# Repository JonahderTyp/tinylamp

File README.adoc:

= tinylamp
Jonah Wille

The tinylamp is a small Headlamp using an ATtiny processor. It is Specifically designed for Scouts, it Features:

* Li-Ion rechargeable Battery
* Charging via Mini-Usb <<Why Mini-Usb?>>

A headlamp specifically designed for scouts

== Overview

image::doc/UserManual/pages/figures/case.png[alt]

== Design Decisions:

=== Why Mini-Usb?

Mini USB is a very durable connector, while USB-C is very susceptible to dust and dirt. Furthermore, Mini USB is easy to handsolder using hot air.

[CAUTION]
The charging port does not comply to USB standards, check schematic for further information.

== TO DOs
* [ ] Headband
* [ ] Inter Lamp Communication

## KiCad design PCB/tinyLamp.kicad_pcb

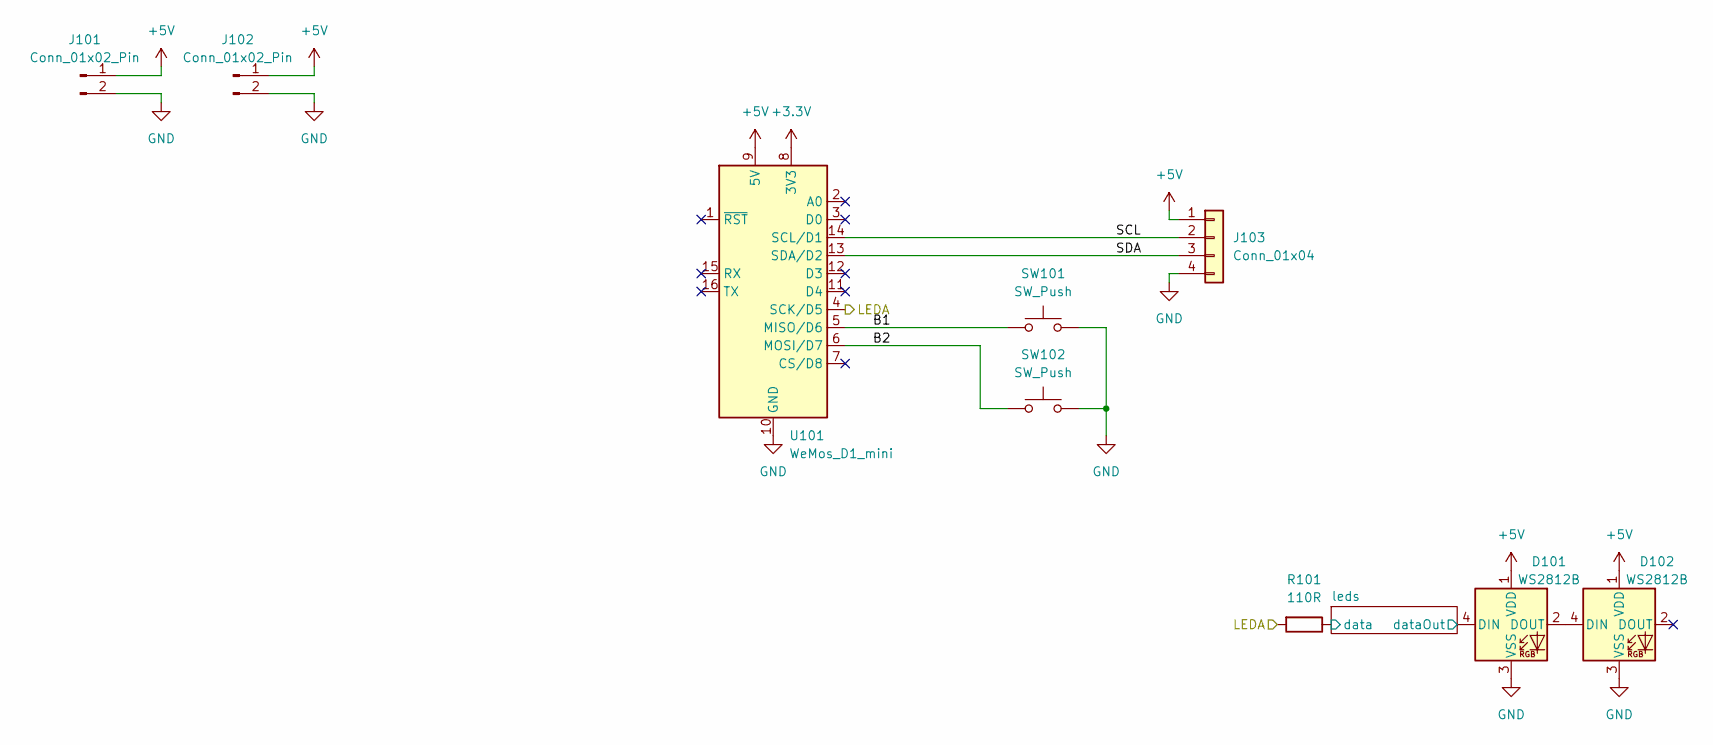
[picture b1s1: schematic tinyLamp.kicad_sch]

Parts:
D101, D102: WS2812B; LED_WS2812B_PLCC4_5.0x5.0mm_P3.2mm
J101, J102: Conn_01x02_Pin; PinHeader_1x02_P2.54mm_Vertical
J103: Conn_01x04; PinHeader_1x04_P2.54mm_Vertical
R101: 110R; R_Axial_DIN0207_L6.3mm_D2.5mm_P10.16mm_Horizontal
SW101, SW102: SW_Push; SW_SPST_PTS647_Sx50
U101: WeMos_D1_mini; WEMOS_D1_mini_light

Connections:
+3.3V: U101.8 (3V3)
+5V: D101.1 (VDD), D102.1 (VDD), J101.1, J102.1, J103.1, U101.9 (5V); also elsewhere on the board
/B1: SW101.1, U101.5 (MISO/D6)
/B2: SW102.1, U101.6 (MOSI/D7)
/LEDA: R101.2, U101.4 (SCK/D5)
/SCL: J103.2, U101.14 (SCL/D1)
/SDA: J103.3, U101.13 (SDA/D2)
/leds/data: R101.1; also elsewhere on the board
/leds/dataOut: D101.4 (DIN); also elsewhere on the board
GND: D101.3 (VSS), D102.3 (VSS), J101.2, J102.2, J103.4, SW101.2, SW102.2, U101.10 (GND); also elsewhere on the board
unnamed: D101.2 (DOUT), D102.4 (DIN)

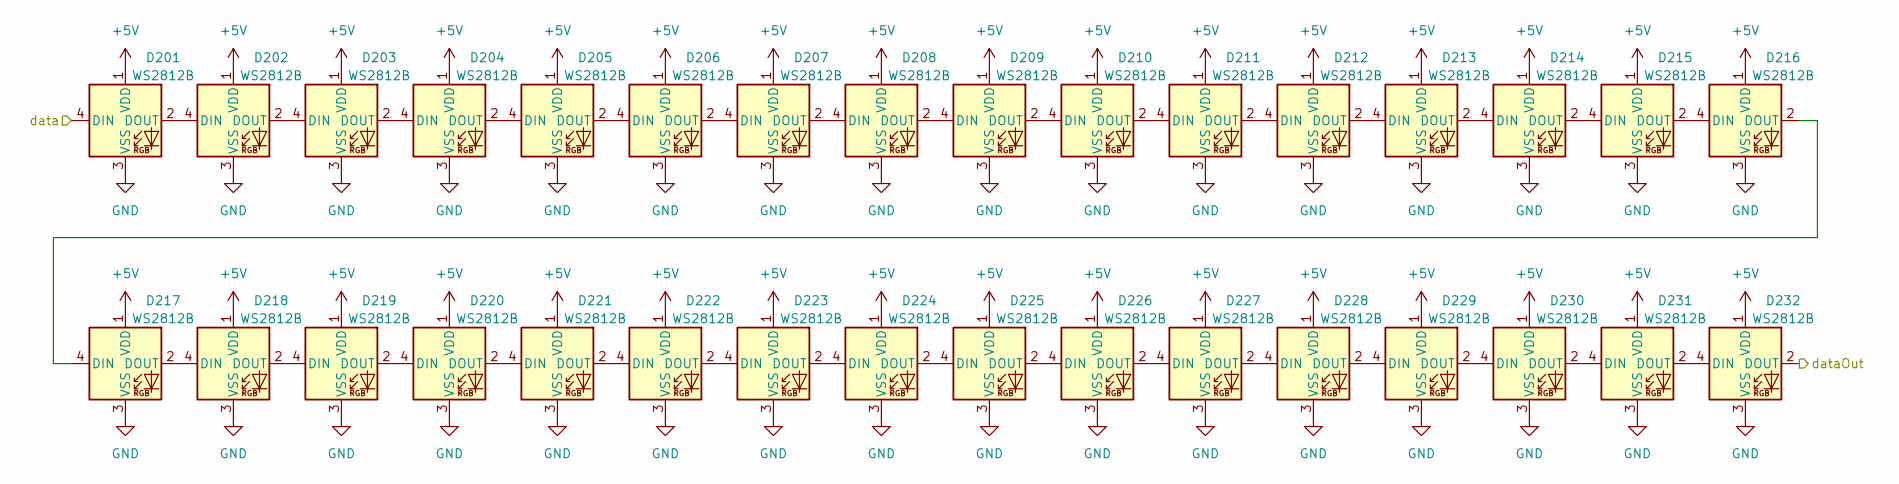
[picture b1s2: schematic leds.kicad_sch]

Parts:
D201, D202, D203, D204, D205, D206, D207, D208, D209, D210, D211, D212, D213, D214, D215, D216, D217, D218, D219, D220, D221, D222, D223, D224, D225, D226, D227, D228, D229, D230, D231, D232: WS2812B; LED_WS2812B_PLCC4_5.0x5.0mm_P3.2mm

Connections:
+5V: D201.1 (VDD), D202.1 (VDD), D203.1 (VDD), D204.1 (VDD), D205.1 (VDD), D206.1 (VDD), D207.1 (VDD), D208.1 (VDD), D209.1 (VDD), D210.1 (VDD), D211.1 (VDD), D212.1 (VDD), D213.1 (VDD), D214.1 (VDD), D215.1 (VDD), D216.1 (VDD), D217.1 (VDD), D218.1 (VDD), D219.1 (VDD), D220.1 (VDD), D221.1 (VDD), D222.1 (VDD), D223.1 (VDD), D224.1 (VDD), D225.1 (VDD), D226.1 (VDD), D227.1 (VDD), D228.1 (VDD), D229.1 (VDD), D230.1 (VDD), D231.1 (VDD), D232.1 (VDD); also elsewhere on the board
/leds/data: D201.4 (DIN); also elsewhere on the board
/leds/dataOut: D232.2 (DOUT); also elsewhere on the board
GND: D201.3 (VSS), D202.3 (VSS), D203.3 (VSS), D204.3 (VSS), D205.3 (VSS), D206.3 (VSS), D207.3 (VSS), D208.3 (VSS), D209.3 (VSS), D210.3 (VSS), D211.3 (VSS), D212.3 (VSS), D213.3 (VSS), D214.3 (VSS), D215.3 (VSS), D216.3 (VSS), D217.3 (VSS), D218.3 (VSS), D219.3 (VSS), D220.3 (VSS), D221.3 (VSS), D222.3 (VSS), D223.3 (VSS), D224.3 (VSS), D225.3 (VSS), D226.3 (VSS), D227.3 (VSS), D228.3 (VSS), D229.3 (VSS), D230.3 (VSS), D231.3 (VSS), D232.3 (VSS); also elsewhere on the board
unnamed: D201.2 (DOUT), D202.4 (DIN)
unnamed: D202.2 (DOUT), D203.4 (DIN)
unnamed: D203.2 (DOUT), D204.4 (DIN)
unnamed: D204.2 (DOUT), D205.4 (DIN)
unnamed: D205.2 (DOUT), D206.4 (DIN)
unnamed: D206.2 (DOUT), D207.4 (DIN)
unnamed: D207.2 (DOUT), D208.4 (DIN)
unnamed: D208.2 (DOUT), D209.4 (DIN)
unnamed: D209.2 (DOUT), D210.4 (DIN)
unnamed: D210.2 (DOUT), D211.4 (DIN)
unnamed: D211.2 (DOUT), D212.4 (DIN)
unnamed: D212.2 (DOUT), D213.4 (DIN)
unnamed: D213.2 (DOUT), D214.4 (DIN)
unnamed: D214.2 (DOUT), D215.4 (DIN)
unnamed: D215.2 (DOUT), D216.4 (DIN)
unnamed: D216.2 (DOUT), D217.4 (DIN)
unnamed: D217.2 (DOUT), D218.4 (DIN)
unnamed: D218.2 (DOUT), D219.4 (DIN)
unnamed: D219.2 (DOUT), D220.4 (DIN)
unnamed: D220.2 (DOUT), D221.4 (DIN)
unnamed: D221.2 (DOUT), D222.4 (DIN)
unnamed: D222.2 (DOUT), D223.4 (DIN)
unnamed: D223.2 (DOUT), D224.4 (DIN)
unnamed: D224.2 (DOUT), D225.4 (DIN)
unnamed: D225.2 (DOUT), D226.4 (DIN)
unnamed: D226.2 (DOUT), D227.4 (DIN)
unnamed: D227.2 (DOUT), D228.4 (DIN)
unnamed: D228.2 (DOUT), D229.4 (DIN)
unnamed: D229.2 (DOUT), D230.4 (DIN)
unnamed: D230.2 (DOUT), D231.4 (DIN)
unnamed: D231.2 (DOUT), D232.4 (DIN)

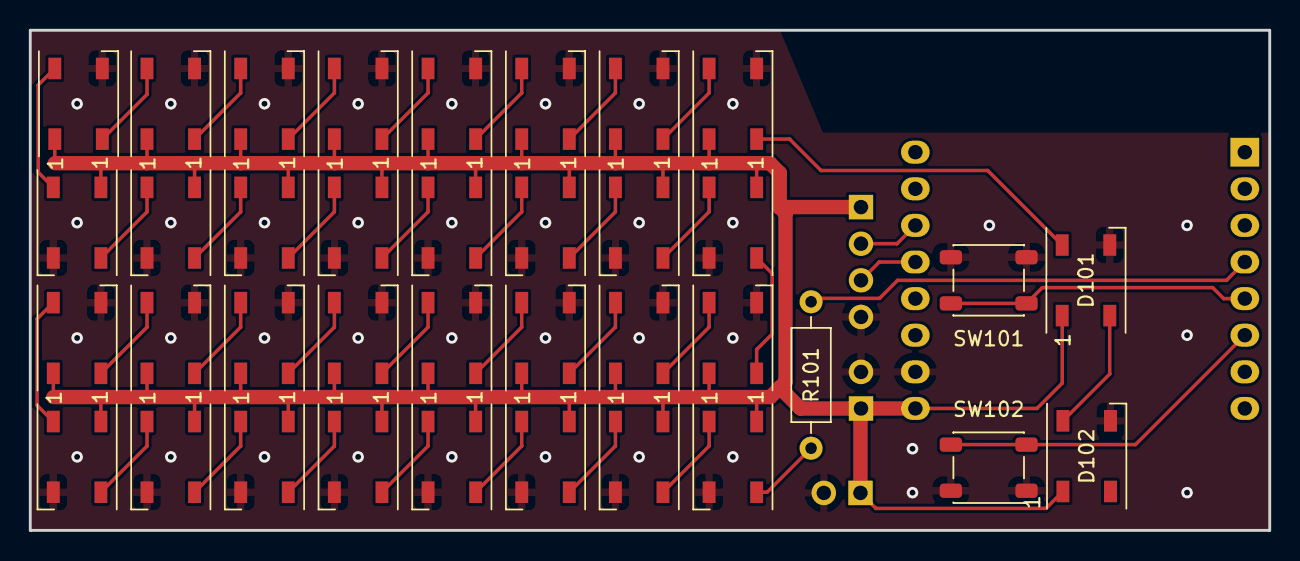
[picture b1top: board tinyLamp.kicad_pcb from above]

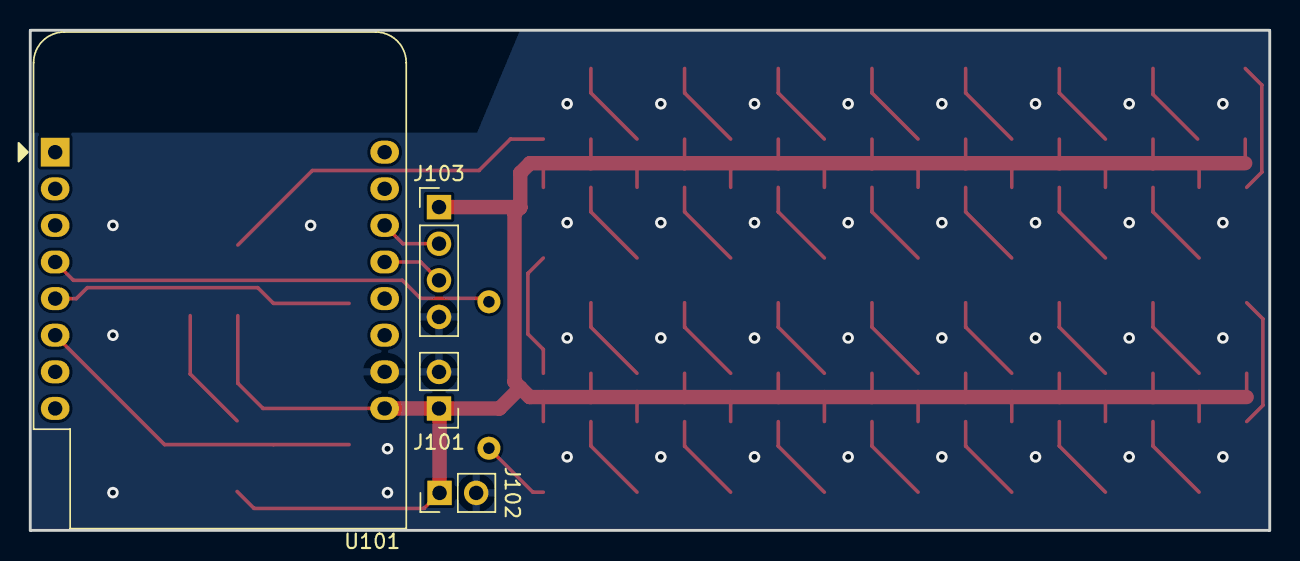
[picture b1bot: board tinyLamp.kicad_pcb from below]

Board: 2 copper layers, 86.0 x 34.7 mm, 41 parts (4 on the bottom side), 41 nets.

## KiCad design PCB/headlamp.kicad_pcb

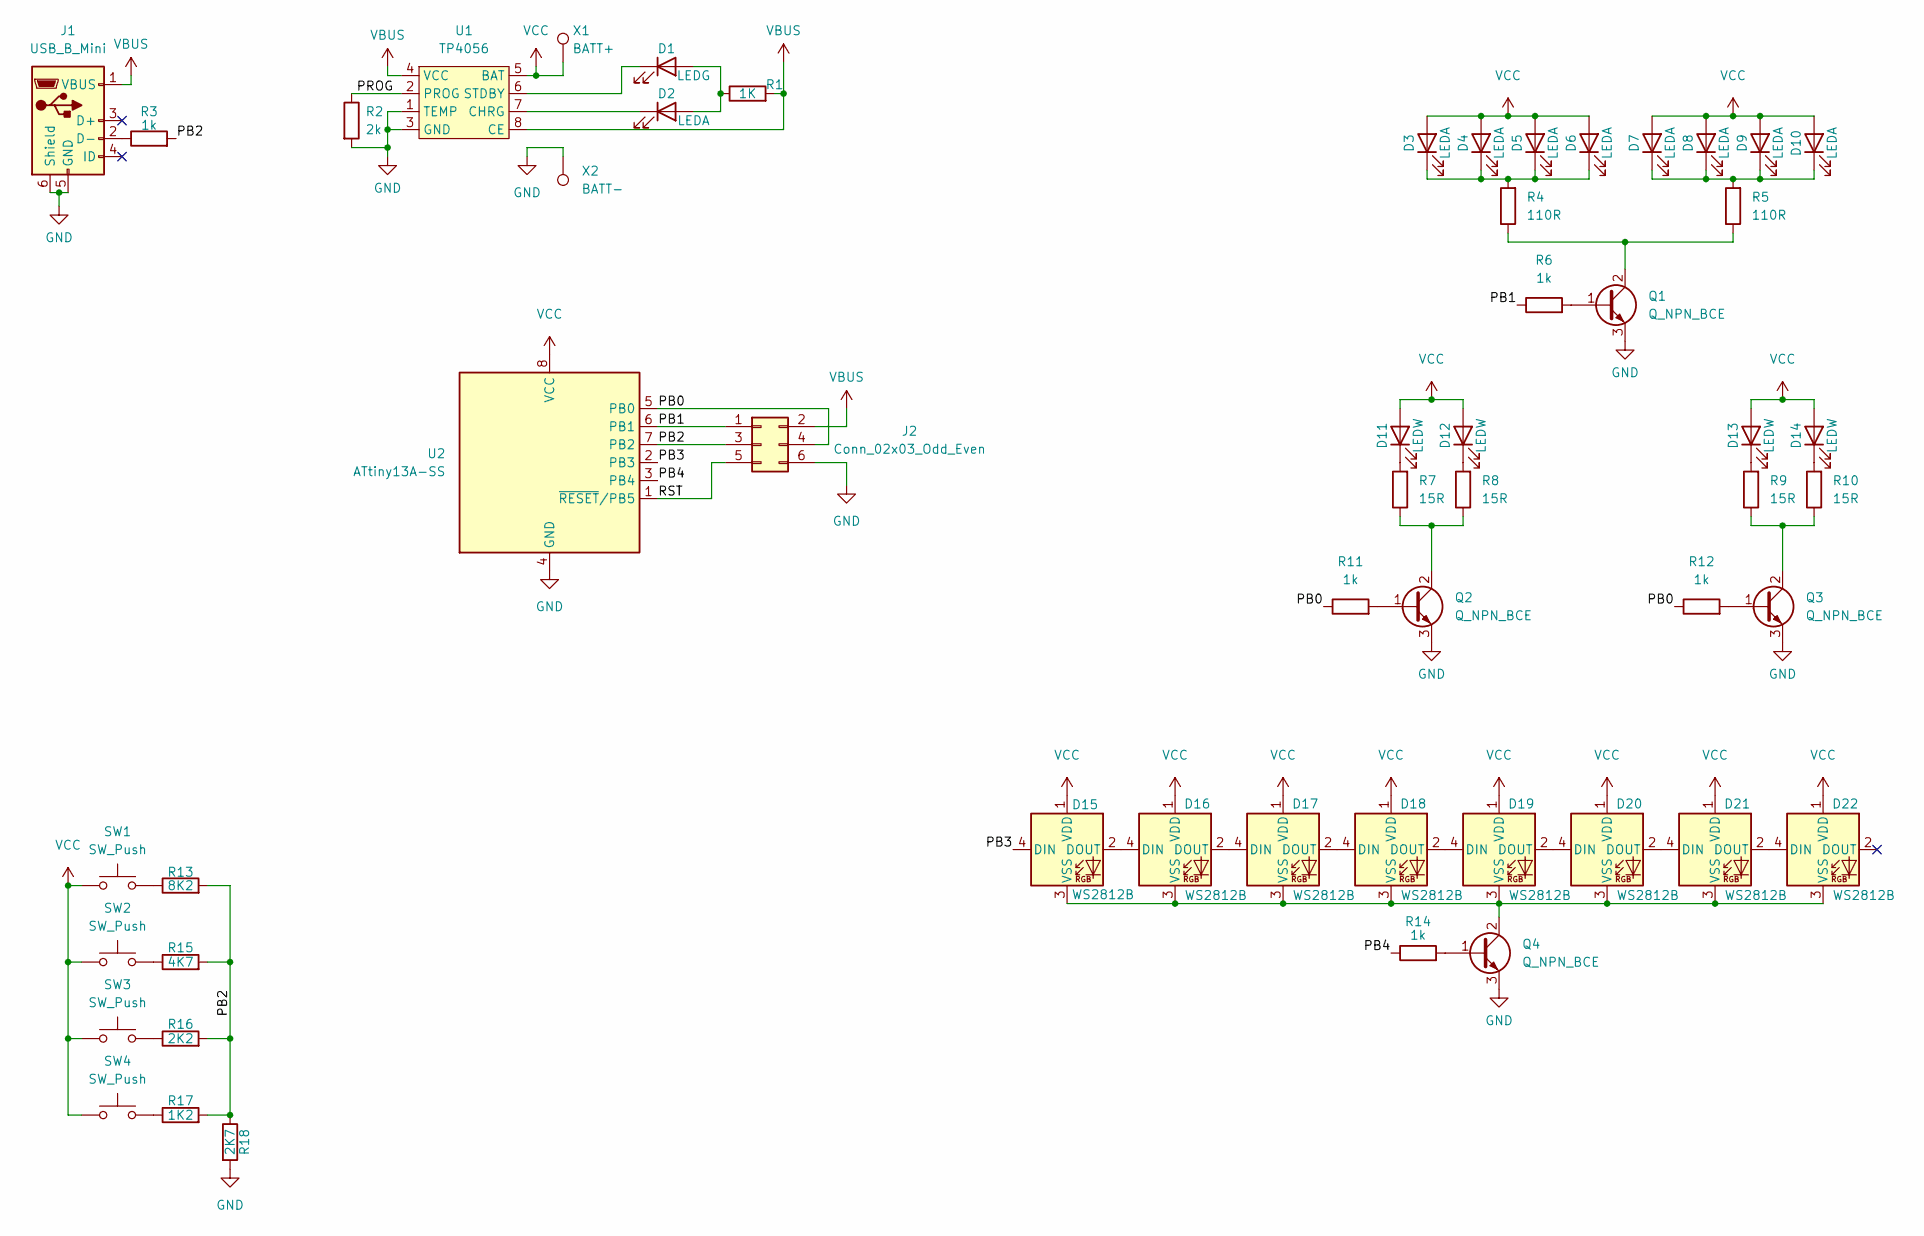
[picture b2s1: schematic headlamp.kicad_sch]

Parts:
D1: LEDG; LED_0805_2012Metric_Pad1.15x1.40mm_HandSolder
D2, D3, D4, D5, D6, D7, D8, D9, D10: LEDA; LED_0805_2012Metric_Pad1.15x1.40mm_HandSolder
D11, D12, D13, D14: LEDW; LED_PLCC-2
D15, D16, D17, D18, D19, D20, D21, D22: WS2812B; LED_WS2812B_PLCC4_5.0x5.0mm_P3.2mm
J1: USB_B_Mini; USB_Mini-B_Lumberg_2486_01_Horizontal
J2: Conn_02x03_Odd_Even; PinHeader_2x03_P2.54mm_Vertical
Q1, Q2, Q3, Q4: Q_NPN_BCE; SOT-23
R1: 1K; R_1206_3216Metric_Pad1.30x1.75mm_HandSolder
R2: 2k; R_1206_3216Metric_Pad1.30x1.75mm_HandSolder
R3, R6, R11, R12, R14: 1k; R_1206_3216Metric_Pad1.30x1.75mm_HandSolder
R4, R5: 110R; R_1206_3216Metric_Pad1.30x1.75mm_HandSolder
R7, R8, R9, R10: 15R; R_1206_3216Metric_Pad1.30x1.75mm_HandSolder
R13: 8K2; R_1206_3216Metric_Pad1.30x1.75mm_HandSolder
R15: 4K7; R_1206_3216Metric_Pad1.30x1.75mm_HandSolder
R16: 2K2; R_1206_3216Metric_Pad1.30x1.75mm_HandSolder
R17: 1K2; R_1206_3216Metric_Pad1.30x1.75mm_HandSolder
R18: 2K7; R_1206_3216Metric_Pad1.30x1.75mm_HandSolder
SW1, SW2, SW3, SW4: SW_Push; SW_SPST_CK_RS282G05A3
U1: TP4056; HSOP-8-1EP_3.9x4.9mm_P1.27mm_EP2.3x2.3mm
U2: ATtiny13A-SS; SOIC-8_3.9x4.9mm_P1.27mm
X1: BATT+; TestPoint_Keystone_5015_Micro-Minature
X2: BATT-; TestPoint_Keystone_5015_Micro-Minature

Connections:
/PB0: J2.4, R11.1, R12.1, U2.5 (PB0)
/PB1: J2.1, R6.1, U2.6 (PB1)
/PB2: J2.3, R3.2, R13.2, R15.2, R16.2, R17.2, R18.1, U2.7 (PB2)
/PB3: D15.4 (DIN), U2.2 (PB3)
/PB4: R14.1, U2.3 (PB4)
/PROG: R2.1, U1.2 (PROG)
/RST: J2.5, U2.1 (~RESET/PB5)
GND: J1.5 (GND), J1.6 (Shield), J2.6, Q1.3 (E), Q2.3 (E), Q3.3 (E), Q4.3 (E), R2.2, R18.2, U1.1 (TEMP), U1.3 (GND), U2.4 (GND), X2.1
unnamed: D1.1 (K), U1.6 (STDBY)
unnamed: D1.2 (A), D2.2 (A), R1.1
unnamed: D2.1 (K), U1.7 (CHRG)
unnamed: D3.1 (K), D4.1 (K), D5.1 (K), D6.1 (K), R4.2
unnamed: D7.1 (K), D8.1 (K), D9.1 (K), D10.1 (K), R5.2
unnamed: D11.1 (K), R7.2
unnamed: D12.1 (K), R8.2
unnamed: D13.1 (K), R9.2
unnamed: D14.1 (K), R10.2
unnamed: D15.2 (DOUT), D16.4 (DIN)
unnamed: D15.3 (VSS), D16.3 (VSS), D17.3 (VSS), D18.3 (VSS), D19.3 (VSS), D20.3 (VSS), D21.3 (VSS), D22.3 (VSS), Q4.2 (C)
unnamed: D16.2 (DOUT), D17.4 (DIN)
unnamed: D17.2 (DOUT), D18.4 (DIN)
unnamed: D18.2 (DOUT), D19.4 (DIN)
unnamed: D19.2 (DOUT), D20.4 (DIN)
unnamed: D20.2 (DOUT), D21.4 (DIN)
unnamed: D21.2 (DOUT), D22.4 (DIN)
unnamed: J1.2 (D-), R3.1
unnamed: Q1.1 (B), R6.2
unnamed: Q1.2 (C), R4.1, R5.1
unnamed: Q2.1 (B), R11.2
unnamed: Q2.2 (C), R7.1, R8.1
unnamed: Q3.1 (B), R12.2
unnamed: Q3.2 (C), R9.1, R10.1
unnamed: Q4.1 (B), R14.2
unnamed: R13.1, SW1.2
unnamed: R15.1, SW2.2
unnamed: R16.1, SW3.2
unnamed: R17.1, SW4.2
VBUS: J1.1 (VBUS), J2.2, R1.2, U1.4 (VCC), U1.8 (CE)
VCC: D3.2 (A), D4.2 (A), D5.2 (A), D6.2 (A), D7.2 (A), D8.2 (A), D9.2 (A), D10.2 (A), D11.2 (A), D12.2 (A), D13.2 (A), D14.2 (A), D15.1 (VDD), D16.1 (VDD), D17.1 (VDD), D18.1 (VDD), D19.1 (VDD), D20.1 (VDD), D21.1 (VDD), D22.1 (VDD), SW1.1, SW2.1, SW3.1, SW4.1, U1.5 (BAT), U2.8 (VCC), X1.1

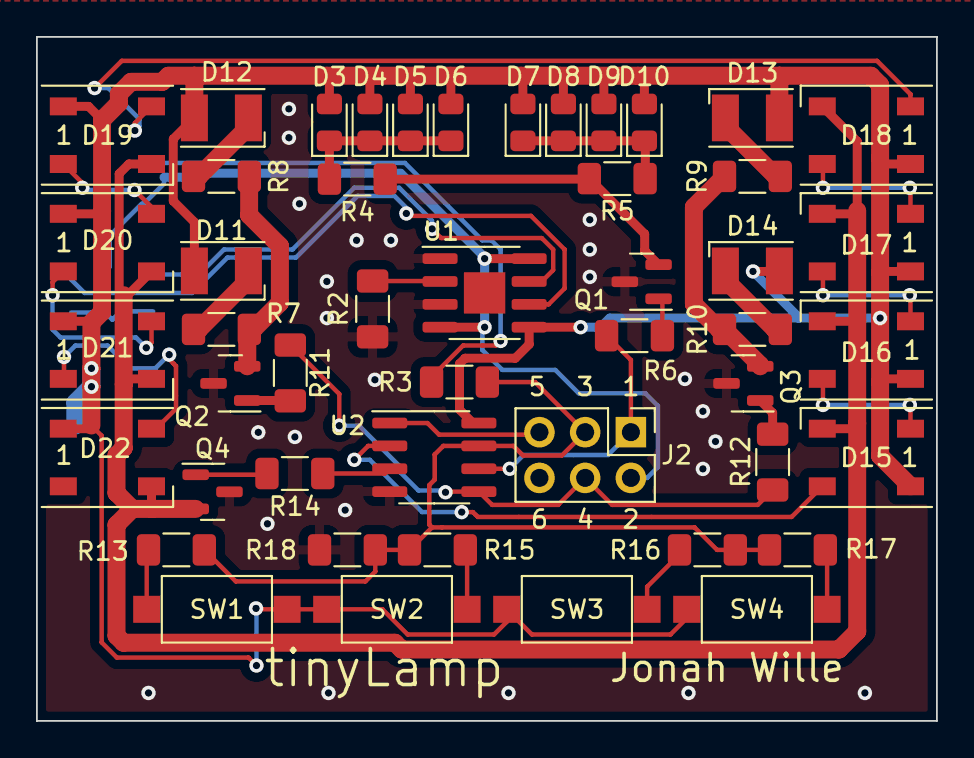
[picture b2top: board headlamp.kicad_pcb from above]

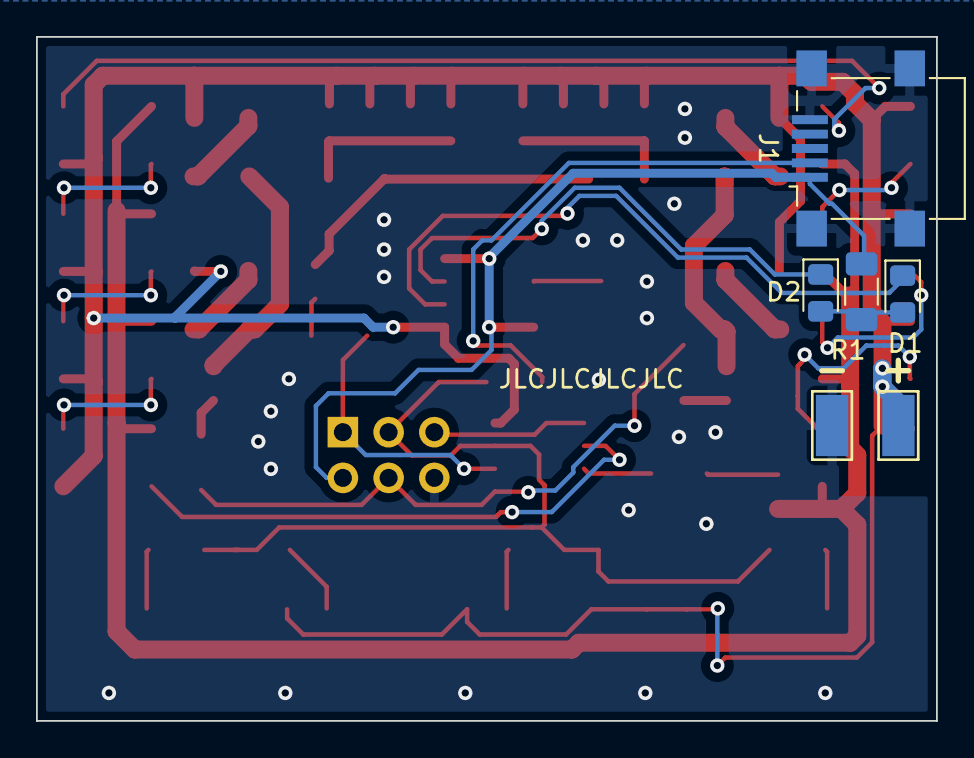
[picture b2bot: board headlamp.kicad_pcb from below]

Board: 2 copper layers, 50.0 x 38.0 mm, 54 parts (6 on the bottom side), 39 nets.

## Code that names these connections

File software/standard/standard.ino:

#include <avr/io.h>
#include <avr/interrupt.h>
#include <util/delay.h>
#include <Arduino.h>
#include "pwm.h"
#include "aled.h"
#include "adc.h"
#include "colors.h"


#define LEDW (PB0)
#define LEDA (PB1)
#define SWIN (PB2)
#define ALED (PB3)
#define ALEDEN (PB4)

#define PIXEL_NUM (8)

uint8_t countr = 0;

uint64_t halfMillis = 0;


ISR(TIM0_OVF_vect) {
  halfMillis++;
  //countr++;
  //PORTB ^= _BV(LEDW); // toggle LED pin
}

struct pixel {
  uint8_t g;
  uint8_t r;
  uint8_t b;
} pixels[PIXEL_NUM];


int main(void) {
  DDRB |= _BV(LEDW) | _BV(LEDA) | _BV(ALED) | _BV(ALEDEN);
  PORTB |= (_BV(LEDW) | _BV(LEDA) | _BV(ALEDEN));

  //struct pixel p = { 0, 10, 0 };


  //mode
  uint8_t mode = 0;

  //pwm
  uint8_t ch0, ch1;
  pwm_init();
  pwm_set_frequency(N_8);
  pwm_set_duty0inv(0);
  pwm_set_duty1inv(0);


  //adc
  adc_init();
  uint16_t data = 0;

  //flashing
  TIMSK0 |= _BV(TOIE0);  // enable Timer Overflow interrupt
  sei();                 // enable global interrupts
  uint8_t flashcounter = 0;
  uint64_t lastflash = 0;
  uint16_t doubleinterval = 40;  //~10ms



  /* loop */
  while (1) {

    if (halfMillis - lastflash >= doubleinterval) {
      lastflash = halfMillis;
      flashcounter++;
      //PORTB |= _BV(ALEDEN);
    }

    //PORTB &= ~_BV(ALEDEN);

    struct pixel p = { 0, 0, 0 };

    switch (mode) {
      case 1:
        switch (flashcounter) {
          case 0:
          case 9:
          case 18:
            //p = {ORANGE};
            break;
          case 7:
          case 16:
          case 25:
            p = { 0, 0, 0 };
            break;
          case 42:
            flashcounter = -1;
            break;
            break;
        }
    }

    for (int i = 0; i < PIXEL_NUM; ++i)
      pixels[i] = p;
    ws2812_setleds((struct cRGB *)pixels, PIXEL_NUM);

    //ALED Turn off
    /*PORTB &= ~_BV(ALED);
    PORTB |= _BV(ALEDEN);
    _delay_ms(5);

    for (int i = 0; i < PIXEL_NUM; ++i)
      pixels[i] = { 255, 255, 255 };
    ws2812_setleds((struct cRGB *)pixels, PIXEL_NUM);

    _delay_ms(100);

    PORTB |= _BV(ALED);
    PORTB &= ~_BV(ALEDEN);

    _delay_ms(200);*/

    //uint16_t data = map(adc_read(),0,1023,0,255);
    //uint16_t data = adc_readB();
    //data = 0xFFFF;
    //data++;
    //uint16_t data = 0x03FF;


    //duty++;

    //if(duty == 255){
    //pwm_stop();
    //}

    //p.r = duty;
    //p.g = duty;
    //p.b = duty;

    /*for (int i = 0; i < PIXEL_NUM; ++i) {
      if ((countr >> i) & 0x01) {
        pixels[i] = pixel{ 0, 20, 0 };
      } else {
        pixels[i] = pixel{ 0, 0, 0 };
      }
    }

    ws2812_setleds((struct cRGB *)pixels, PIXEL_NUM);*/

    //countr = 1;

    //PORTB |= ((halfMillis & 0x01) << ALEDEN);
    //PORTB &= ((halfMillis & 0x01) << ALEDEN);

    //PORTB &= (1 << _BV(ALEDEN));

    /*for (int i = 0; i < 2; i++) {

      for (int i = 0; i < PIXEL_NUM; ++i)
        pixels[i] = pixel{ 0,0, 0 };
        //pixels[i] = pixel{ ORANGE };
      ws2812_setleds((struct cRGB *)pixels, PIXEL_NUM);
      _delay_ms(70);
      for (int i = 0; i < PIXEL_NUM; ++i)
        pixels[i] = pixel{ 0, 0, 0 };
      ws2812_setleds((struct cRGB *)pixels, PIXEL_NUM);
      _delay_ms(20);
    }*/
    //PORTB |= _BV(ALEDEN);

    //_delay_ms(20);
    //PORTB &= ~_BV(ALEDEN);
    //_delay_ms(150);
  }
}

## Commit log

2022-11-19 firstbackup
2022-11-20 USB con overhang pcb
2022-11-20 added documentation
2022-11-20 renamed pwm functions
2022-11-20 added mode switchcase
2022-11-20 updated 3d model
2022-11-20 Renamed KiCad Project
2022-11-20 removed old project file
2022-11-20 updated gitignore
2022-11-20 Added PCB path for KiCad ignore
2022-11-20 moved usb con inside board parameters
2022-12-07 switches are using rst pin
2022-12-24 made Sub schematics
2023-02-10 made some Changes
2023-02-10 added Capacitor and updated PCB
2023-02-10 Moved schematic 3 and 4
2023-03-04 made some changes on RGB LEDs
2023-03-04 renamed Software to src
2023-03-20 added Image to Readme
2024-07-07 Updated Schematic to use Wemos D1 and external Power
2024-07-08 uploaded code
2024-07-09 uploaded files
2024-07-09 removed old files
2024-07-09 first working version
2024-07-10 refactor: Update main.cpp with broadcast and MAC addresses
2024-07-11 implemented mac address
2024-07-11 fixed typo
2024-07-11 chore: Refactor message.h to use fixed-size arrays instead of std::array
2024-07-11 refactor: Update ComHandler.h to improve message handling and add MAC address support
2024-07-11 feat: Set MAC address in comHandler.setMacAddress() method
2024-07-11 feat: sending message
2024-07-11 improve readability
2024-07-11 refactor: Update Button class to handle extra long press
2024-07-11 changed broadcast mac address
2024-07-11 refactor: Extract lamp logic into separate function
2024-07-11 feat: added group settings
2024-07-13 refactor: Update Button class to handle short and long press thresholds
2024-07-13 implemented menu
2024-07-13 actually using it
2024-07-13 refactor: Simplify LedController menu method
2024-07-13 added human readable values
2024-07-13 refactor: Update menu function to handle group changes
2024-07-13 decreased long press time
2024-07-13 refactor: Add ESP8266TrueRandom library for generating random message IDs
2024-07-13 feat: Add functionality to send messages on long press of color button
2024-07-13 added blinking
2024-07-13 added set function
2024-07-13 implemented comunication
2024-07-14 refactor: Update sendMsg function to print incoming and outgoing messages
2024-07-14 added doc
2024-07-14 fix: message multiplication
2024-07-14 pcb: placed leds
